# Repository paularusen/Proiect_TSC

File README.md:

## Descrierea produsului

  Proiectul este centrat pe microcontrolerul ```ESP32-C6```, care, datorită versatilității sale, suportă comunicații Wi‑Fi 6, 
Bluetooth și IEEE 802.15.4, alături de multiple interfețe periferice. Designul integrează un e‑paper display, un modul SD 
card, memorie flash externă, un modul RTC și interfețe de comunicație (```USB```, ```UART```, ```I2C```). Fiecare interfață este atribuită 
unor pini specifici pentru a asigura o separare clară a funcțiilor, evitând conflictele și maximizând performanța și
eficiența energetică.

## Diagrama bloc

## Descrierea componentelor și a pinilor utilizați

### ESP32-C6 – Microcontrolerul Central
Rol: Coordonează toate operațiunile sistemului și gestionează comunicațiile cu toate modulele periferice.
Pini atribuiți:

	- GND: 1 si 28
	- 3V3: 2
	- RESET: 3
	- SS_SD: 4
	- EPD_DC: 5
	- SCK: 6
	- MOSI: 7
	- INT_RTC: 8
	- 32KHZ: 9
	- GPIO8: 10
	- EPD_CS: 11
	- FLASH_CS: 12
	- USB_D-: 13
	- USB_D+: 14
	- IO/BOOT: 15
	- RTC_RST: 16
	- I2C_PW: 17
	- EPD_3V3_C: 18
	- SDA: 19
	- SCL: 20
	- EPD_RST: 21
	- IO/CHANGE: 23
	- RX: 24
	- TX: 25
	- EPD_BUSY: 26
	- MISO: 27

Rolul fiecărui pin va fi detaliat în cadrul componentelor, în următoarele rânduri.

### E‑Paper Display
Rol: Afișare informații într-un mod foarte eficient energetic, potrivit pentru aplicații de tip IoT sau afișaje statice.
Pini atribuiți:

	- EPD_DC: Selectează între modurile de comandă și de date pentru e-paper.
	- EPD_CS: Chip Select – activează comunicația cu e‑paper-ul.
	- EPD_RST: Linie de reset, esențială la inițializare pentru afișaj.
	- EPD_BUSY: Semnal de status ce indică dacă afișajul este ocupat (prevenind suprascrierea datelor).
	- EPD_3V3_C: Linia de alimentare dedicată, asigurând o tensiune stabilă și izolată pentru e‑paper.

### Modul SD Card
Rol: Stocare de date suplimentare (fișiere de sistem, date utilizator etc.)
Pini atribuiți:

	- SS_SD: Chip select specific pentru SD Card, activând modulul numai atunci când este necesar.
	- SCK: Linia de ceas pentru comunicațiile SPI.
	- MOSI: Linia de ieșire de date dinspre ESP32 către SD Card.
	- MISO: Linia de intrare de date, pentru citirea informațiilor de la SD Card.

### Memorie Flash Externă
Rol: Stocarea firmware-ului sau a datelor critice ce necesită o capacitate suplimentară față de memoria internă.
Pini atribuiți:

	- FLASH_CS: Chip select pentru memorie flash, pentru a activa comunicația doar atunci când este necesar.

### Modul RTC (Real-Time Clock)
Rol: Asigură o cronometrare precisă, utilă pentru funcții de alarmă, logare a datelor sau sincronizare de timp în 
aplicații IoT.
Pini atribuiți:

	- INT_RTC: Întrerupere de la RTC, notificând microcontrolerul despre evenimente (ex. alarmă).
	- RTC_RST: Linia de reset pentru modulul RTC, asigurând reinițializarea corectă a ceasului.
	- 32KHZ: Furnizează un semnal de 32 kHz, esențial pentru funcționarea precisă a RTC-ului.

### Senzorul de mediu (ex.: BME688):
Rol: Măsoară parametri esențiali precum temperatura, umiditatea, presiunea atmosferică și compoziția gazelor din mediul 
înconjurător.
Comunicarea se realizează prin magistrala I2C, utilizând SDA(linia de date I2C), SCL(linia de ceas I2C) și I2C_PW.

### Interfața I2C
Rol: Comunicare cu senzori, module de monitorizare a bateriei, eventual RTC suplimentar sau alte periferice cu consum 
redus.
Pini atribuiți:

	- SDA: Linia de date pentru comunicația I2C.
	- SCL: Linia de ceas pentru I2C.
	- I2C_PW: Poate fi folosit pentru a activa sau alimenta circuitele periferice I2C (ex. senzori sau monitor de baterie).

### Interfața USB
Rol: Programare, transfer de date sau alimentare în anumite condiții.
Pini atribuiți:

	- USB_D- și USB_D+: Linii diferențiale pentru comunicația USB.

### Interfața UART
Rol: Comunicații seriale pentru debugging, logare sau control extern.
Pini atribuiți:

	- RX: Recepție UART.
	- TX: Transmisie UART.

Pinii speciali precum IO/BOOT și IO/CHAGE permit configurarea modului de pornire și monitorizarea încărcării, iar GP0IO8 
și GOL asigură flexibilitatea pentru extinderi viitoare.
	IO/BOOT: utilizat la pornirea sistemului pentru selectarea modului de boot. Această funcție este esențială pentru a 
intra în modul de programare sau diagnosticare, conform cerințelor de firmware.
	IO/CHAGE: dedicat monitorizării stării de încărcare a sistemului. Acest pin poate fi legat la un circuit de detecție al 
încărcării bateriei sau indicator LED pentru a semnala starea de încărcare.
	GP0IO8: un GPIO general care poate fi folosit pentru extinderi ulterioare (ex. conectarea unui senzor adițional, trigger 
de eveniment etc.).
	Pin 22: funcționalitatea acestui pin poate fi folosită ca ieșire generală pentru semnale de control, cum ar fi activarea 
unor relee, indicatori LED suplimentari sau semnale de sincronizare pentru alte module.

## Consumul de Energie și comunicațiile

### Consumul microcontrolerului:
	- ESP32-C6 dispune de moduri de economisire a energiei (deep sleep) și este optimizat pentru aplicații IoT. Astfel, în 
condiții de standby consumul poate fi redus la câțiva microamperi.

### SPI și I2C:
	- Utilizarea magistralelor SPI (pentru SD Card, flash extern și e‑paper display) și I2C (pentru senzori și monitorizare 
baterie) permite un transfer de date rapid și eficient, dar și o separare logică care contribuie la reducerea 
interferențelor.

### USB și UART:
	- Aceste interfețe sunt folosite mai ales pentru debugging și programare. Deși USB poate implica un consum mai mare când 
este activ, acesta este activ doar în timpul programării sau transferurilor de date.

### Alimentare:
	- Pinul de 3V3) este utilizat pentru alimentarea ESP32-C6 și a modulelor critice, iar alocarea separată pentru EPD 
(EPD_3V3_C) asigură o tensiune stabilă pentru afișajul e-paper.

## Bill of Materials
| Componentă | Distribuitor | Datasheet |
| :---      | :---     | :---      |
| ESP32 C6| https://eu.mouser.com/ProductDetail/Espressif-Systems/ESP32-C6-WROOM-1U-N8?qs=1Kr7Jg1SGW%2FzPU4G%252ByMwkA%3D%3D | https://eu.mouser.com/datasheet/2/891/Espressif_Systems_7_11_2023_esp32_c6_wroom_1_wroom-3236277.pdf |
| BUTTON | https://www.digikey.ro/en/products/detail/bourns-inc/7914S-1-000E/2537971?s=N4IgTCBcDaIOwE4CMAWAygWiRgDHgoiALoC%2BQA | https://www.bourns.com/docs/Product-Datasheets/7914.pdf |
| USB-C connector| https://eu.mouser.com/ProductDetail/Same-Sky/UJC-H-G-SMT-2-P6-TR?qs=IKkN%2F947nfApFV8T6rOqww%3D%3D |https://eu.mouser.com/datasheet/2/1628/ujc_h_g_smt_2_p6_tr-3511211.pdf |
| USBLC6-2SC6Y | https://eu.mouser.com/ProductDetail/STMicroelectronics/USBLC6-2SC6Y?qs=gNDSiZmRJS%2FOgDexvXkdow%3D%3D | https://eu.mouser.com/datasheet/2/389/usblc6_2sc6y-1852505.pdf |
| DMG2305UX-7 | https://eu.mouser.com/ProductDetail/Diodes-Incorporated/DMG2305UX-7?qs=L1DZKBg7t5F%2FNBHrjfxC%252Bg%3D%3D | https://www.diodes.com/assets/Datasheets/DMG2305UX.pdf |
| XC6220A331MR-G | https://eu.mouser.com/ProductDetail/Torex-Semiconductor/XC6220A331MR-G?qs=AsjdqWjXhJ8ZSWznL1J0gg%3D%3D | https://eu.mouser.com/datasheet/2/760/xc6220-3371556.pdf |
| SD0805S020S1R0 | https://eu.mouser.com/ProductDetail/KYOCERA-AVX/SD0805S020S1R0?qs=jCA%252BPfw4LHbpkAoSnwrdjw%3D%3D | https://eu.mouser.com/datasheet/2/40/schottky-3165252.pdf |
| 112A-TAAR-R03 | https://store.comet.srl.ro/Catalogue/Product/43497/ | https://store.comet.bg/download-file.php?id=27596 |
| 68uH inductance | https://eu.mouser.com/ProductDetail/Vishay-Dale/IFDC5050JZER680M?qs=iLKYxzqNS745SePZd8tBoA%3D%3D | https://www.vishay.com/docs/34635/ifdc5050jz.pdf |
| SI1308EDL-T1-GE3 | https://eu.mouser.com/ProductDetail/Vishay-Semiconductors/SI1308EDL-T1-GE3?qs=bX1%252BNvsK%2FBramh9tgpOaEw%3D%3D | https://www.vishay.com/docs/63399/si1308edl.pdf |
| MBR0530 | https://eu.mouser.com/ProductDetail/Micro-Commercial-Components-MCC/MBR0530-TP?qs=KFo7JewZbUECRHkxGanrdg%3D%3D | https://eu.mouser.com/datasheet/2/258/MBR0520_MBR0580_SOD123_-2492194.pdf |
| MCP73831 | https://eu.mouser.com/ProductDetail/Microchip-Technology/MCP73831-2ACI-MC?qs=hH%252BOa0VZEiBneYTVdpuVdg%3D%3D | https://eu.mouser.com/datasheet/2/268/MCP73831_Family_Data_Sheet_DS20001984H-3441711.pdf |
| BME688 | https://eu.mouser.com/ProductDetail/Bosch-Sensortec/BME688?qs=IS%252B4QmGtzzqQoVDscqwx3A%3D%3D | https://eu.mouser.com/datasheet/2/783/bst_bme688_fl000-2307034.pdf |
| FH34SRJ-24S-0.5SH(99) | https://eu.mouser.com/ProductDetail/Hirose-Connector/FH34SRJ-24S-0.5SH99?qs=vcbW%252B4%252BSTIpKBl5ap9J8Fw%3D%3D | https://eu.mouser.com/datasheet/2/185/FH34SRJ_24S_0_5SH_99__CL0580_1255_6_99_2DDrawing_0-1615044.pdf |
| BD5229G-TR | https://eu.mouser.com/ProductDetail/ROHM-Semiconductor/BD5229G-TR?qs=4kLU8WoGk0vvnhrrYwdszw%3D%3D | https://fscdn.rohm.com/en/products/databook/datasheet/ic/power/voltage_detector/bd52xxg-e.pdf |
| MAX17048G+T10 | https://eu.mouser.com/ProductDetail/Analog-Devices-Maxim-Integrated/MAX17048G%2bT10?qs=D7PJwyCwLAoGnnn8jEPRBQ%3D%3D | https://eu.mouser.com/datasheet/2/609/MAX17048_MAX17049-3469099.pdf |
| DS3231SN# | https://eu.mouser.com/ProductDetail/Analog-Devices-Maxim-Integrated/DS3231SN?qs=1eQvB6Dk1vhUlr8%2FOrV0Fw%3D%3D | https://eu.mouser.com/datasheet/2/609/DS3231-3421123.pdf |
| CPH3225A | https://eu.mouser.com/ProductDetail/Seiko-Semiconductors/CPH3225A?qs=3etwrb1wR%252BhUOph6lAO7eg%3D%3D | https://eu.mouser.com/datasheet/2/360/Seiko_Instruments_MicroBattery_E_20230330_2024Jan_-3561061.pdf |
| PFMF.050.1 | https://eu.mouser.com/ProductDetail/Schurter/PFMF.050.2?qs=1auRipcfynCums5v1iucSA%3D%3D | https://eu.mouser.com/datasheet/2/358/typ_PFMF-1275918.pdf |
| Qwiic | https://eu.mouser.com/ProductDetail/Adafruit/4208?qs=PzGy0jfpSMtbScLbr0L5dw%3D%3D | https://learn.adafruit.com/introducing-adafruit-stemma-qt/technical-specs |
| W25Q512JVEIQ | https://eu.mouser.com/ProductDetail/Winbond/W25Q512JVEIQ?qs=l7cgNqFNU1jw6svr3at6tA%3D%3D | https://eu.mouser.com/datasheet/2/949/Winbond_W25Q512JV_Datasheet-3240039.pdf |
| PGB1010603MR | https://eu.mouser.com/ProductDetail/Littelfuse/PGB1010603MR?qs=gu7KAQ731URLg4GSnNNN7Q%3D%3D | https://www.littelfuse.com/assetdocs/pulseguard-esd-suppressors-pgb1-datasheet?assetguid=8a337998-d54d-466b-be4e-dc5bcd1f9321 |
| TANT Capacitor | https://eu.mouser.com/ProductDetail/KEMET/T491B107M006AT?qs=U312oeP%2FpiHOgyk6KO2m0g%3D%3D | https://www.vishay.com/docs/40002/293d.pdf |
| Capacitor 0.1uF | https://eu.mouser.com/ProductDetail/KYOCERA-AVX/KGF21BR71H104KT?qs=Jm2GQyTW%2FbjYyKCvVWAEOw%3D%3D | https://eu.mouser.com/datasheet/2/40/KGF-3223650.pdf |
| Capacitor 1uF | https://eu.mouser.com/ProductDetail/TAIYO-YUDEN/MAASL105CC7105MFCA01?qs=HFfMDpzxxd1Fn%2FInbJA7vw%3D%3D | https://eu.mouser.com/datasheet/2/396/TAIYO_YUDEN_04_27_2024_c_mlcc_A_e1-3451516.pdf |
| Capacitor 4.7uF | https://eu.mouser.com/ProductDetail/KYOCERA-AVX/CM05X5R475M16AH?qs=doiCPypUmgFT1xquZKhWtQ%3D%3D | https://eu.mouser.com/datasheet/2/40/Kyocera_AVX_Components_CM025_CM05_CM105_CM21_E217K-2932876.pdf |
| Capacitor 10 uF | https://eu.mouser.com/ProductDetail/TDK/CGA3EDX7T1A106M080AU?qs=ZcfC38r4PovL%2FBNBUzzBFw%3D%3D | https://product.tdk.com/system/files/dam/doc/product/capacitor/ceramic/mlcc/catalog/mlcc_automotive_general_en.pdf |
| Capacitor 100nF | https://eu.mouser.com/ProductDetail/KYOCERA-AVX/KAM21BR71H104JT?qs=Jm2GQyTW%2Fbic6Zk4McEt6w%3D%3D | https://eu.mouser.com/datasheet/2/40/AutoMLCCKAM-3216307.pdf |
| Resistor 0.47 | https://eu.mouser.com/ProductDetail/SEI-Stackpole/RNCL1210FT50L0?qs=17ckDYBRdelVLOJ%252BDFjlUw%3D%3D | https://eu.mouser.com/datasheet/2/385/sei_rncl-3223524.pdf |
| Resistor 2.2 | https://eu.mouser.com/ProductDetail/YAGEO/RT1206FRE072R2L?qs=XhSZopxZ3H6S0nYZD83pAA%3D%3D | https://eu.mouser.com/datasheet/2/447/PYu_RT_1_to_0_01_RoHS_L_15-3461507.pdf |
| Resistor 15 | https://eu.mouser.com/ProductDetail/Panasonic/ERA-6AHD150V?qs=MNPzkKEzRtQip8ZeekU%252BRw%3D%3D | https://industrial.panasonic.com/cdbs/www-data/pdf/RDM0000/AOA0000C307.pdf |
Resistor 200 | https://eu.mouser.com/ProductDetail/TE-Connectivity-Holsworthy/RP73C2B200RFTDF?qs=n4i9pByFsMR0dWGpf721CA%3D%3D | https://eu.mouser.com/datasheet/2/418/10/ENG_DS_1773272_M1-1588495.pdf |
| Resistor 2k | https://eu.mouser.com/ProductDetail/Panasonic/ERA-3AED202V?qs=yocZuyCaXdM2cBmjcGkIyA%3D%3D | https://industrial.panasonic.com/cdbs/www-data/pdf/RDM0000/AOA0000C307.pdf |
| Resistor 5k1 | https://eu.mouser.com/ProductDetail/Vishay-Beyschlag/MCS04020C5101FE000?qs=wTZ%2FFzl837YsKPLPRIXUbg%3D%3D | https://www.vishay.com/docs/28705/mcx0x0xpro.pdf |
| Resistor 10k | https://eu.mouser.com/ProductDetail/SEI-Stackpole/RNWA0612BTE10K0?qs=IKkN%2F947nfD62pDKWE9ZTQ%3D%3D | https://eu.mouser.com/datasheet/2/385/SEI_RNWA-3473840.pdf |
| Resistor 100K | https://eu.mouser.com/ProductDetail/Panasonic/ERA-3AED104V?qs=MNPzkKEzRtQIWcmUWL4kjg%3D%3D | https://industrial.panasonic.com/cdbs/www-data/pdf/RDM0000/AOA0000C307.pdf |
| E-Paper Display | https://eu.mouser.com/ProductDetail/Microtips-Technology/MT-DEPG0750BNU590F1?qs=DPoM0jnrROVRMMTX0WzK%252Bw%3D%3D| https://eu.mouser.com/datasheet/2/271/MT_DEPG0750BNU590F1_V2_7-1894282.pdf |
| LP584174 Battery| https://www.tme.eu/en/details/accu-lp584174_cl/rechargeable-batteries/cellevia-batteries/l584174/ | https://www.tme.eu/Document/e0683d8c34e6d878124489f71bffb6ee/cel0014.pdf |

## Observații
- Am modificat footprint-ul componentei J2, prin mutarea pad-urilor GND, VUSB și B8 cu câțiva mm spre stânga, pentru a corecta eroarea ”SMD Hole”.

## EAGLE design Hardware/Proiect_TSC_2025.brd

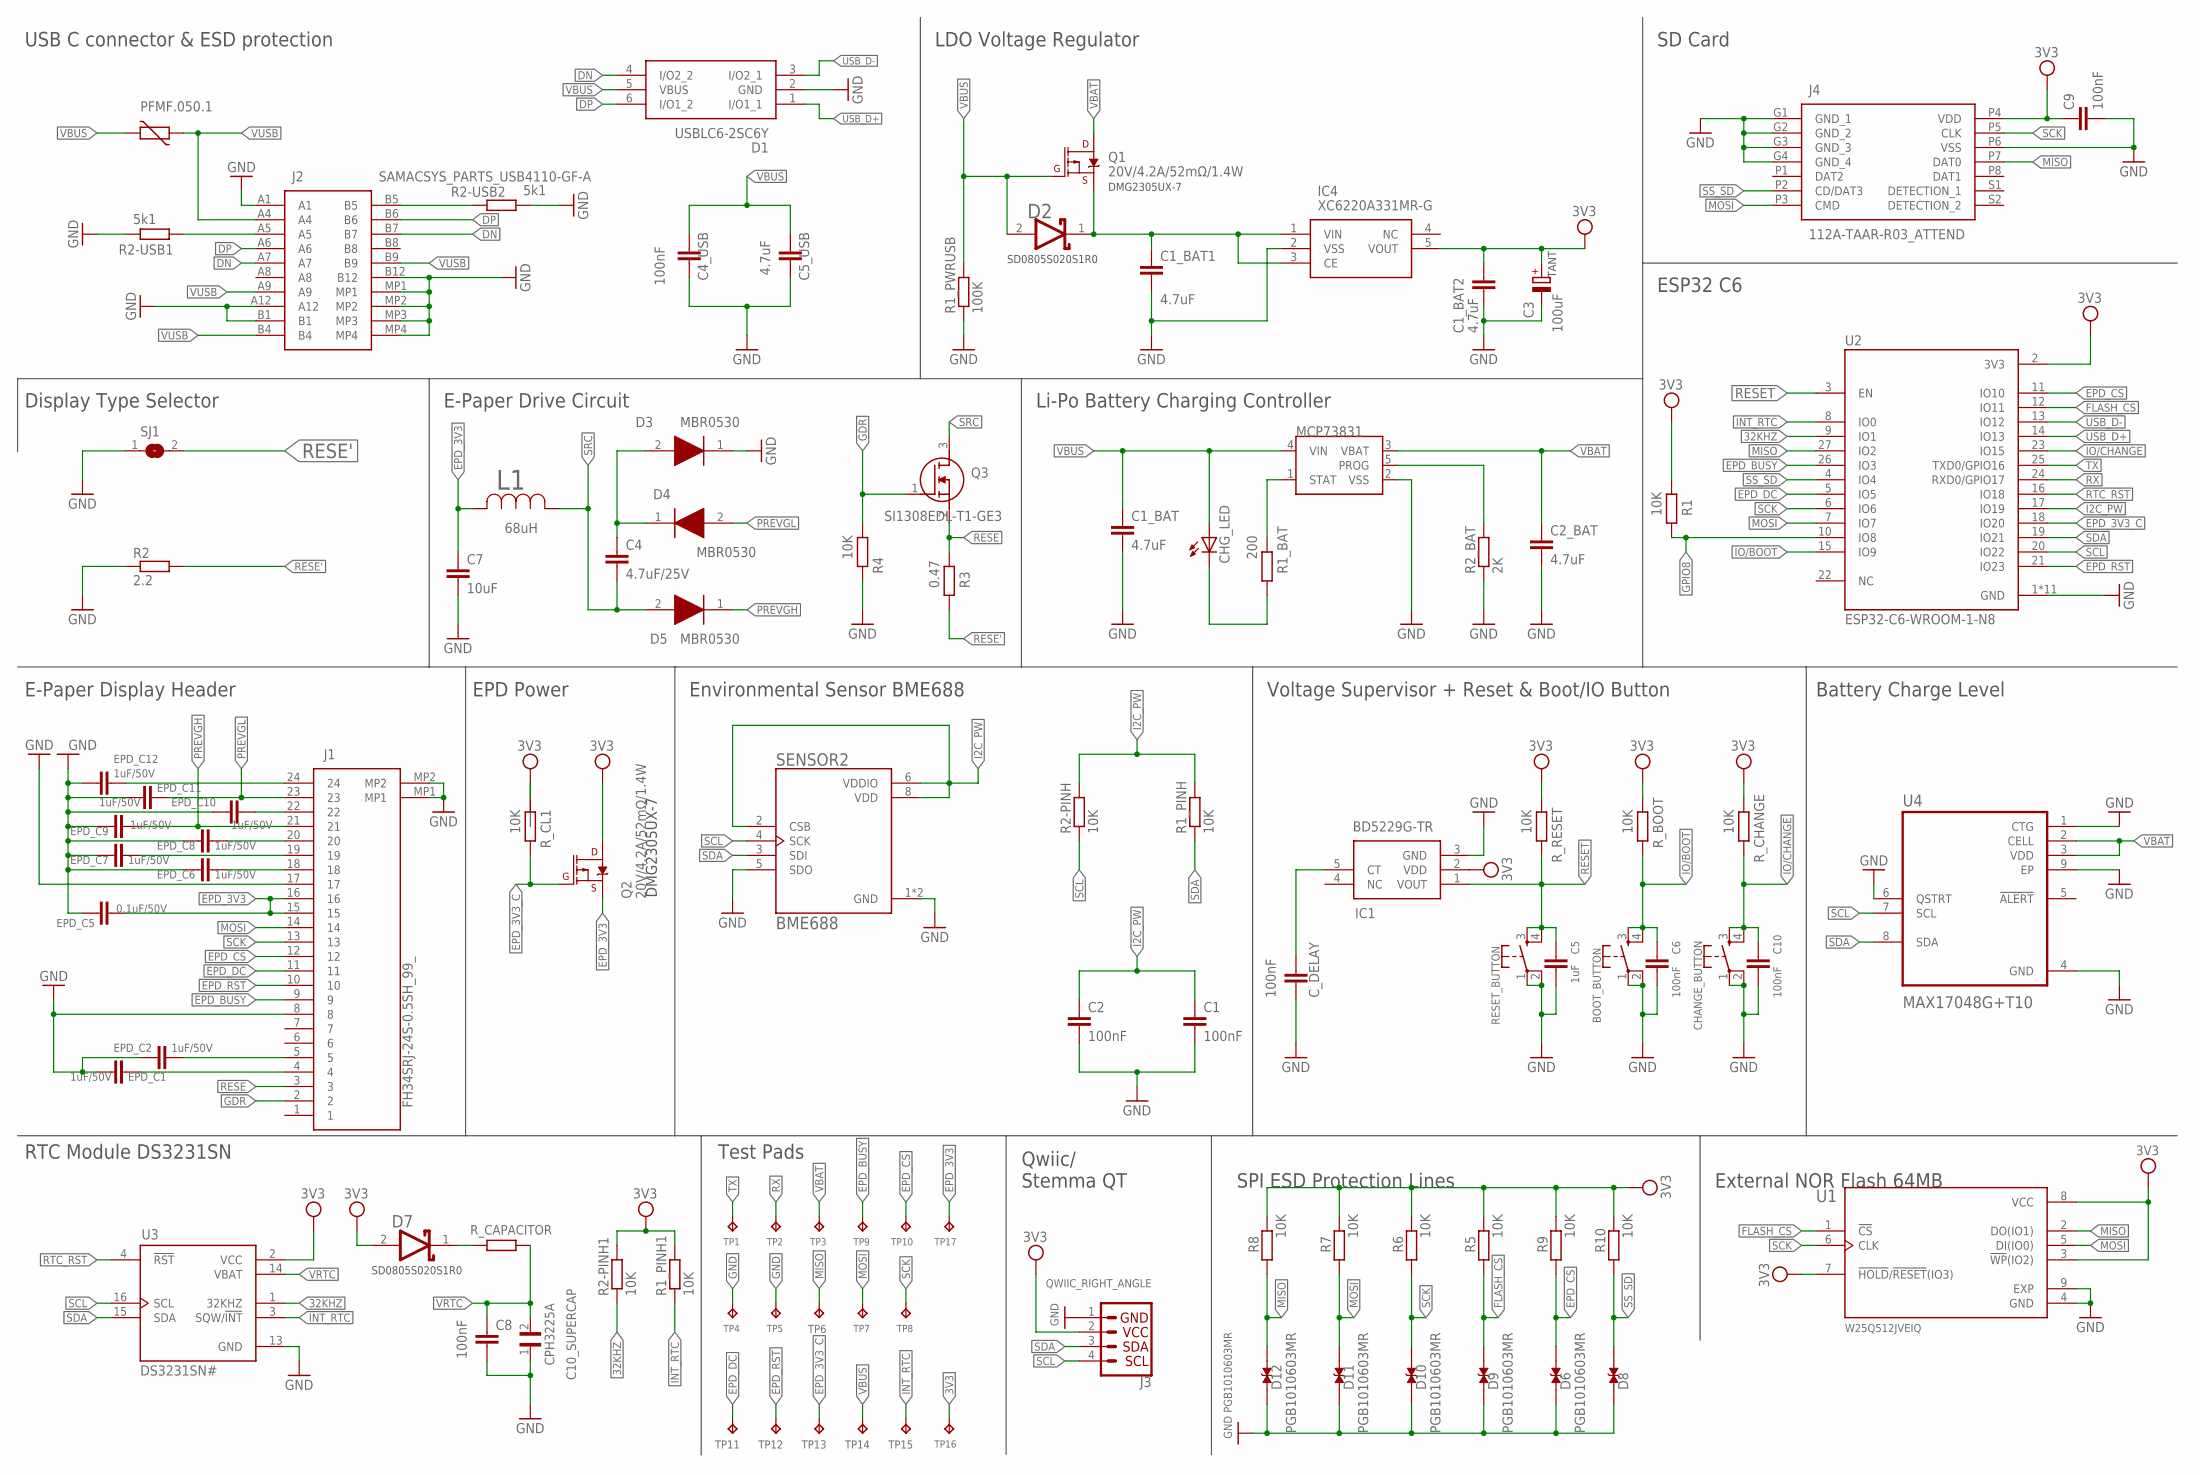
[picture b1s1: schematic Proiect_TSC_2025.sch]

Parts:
BOOT_BUTTON: BUTTON_CUSYOMV1; MYBUTTON
C1, C2, C6, C8, C9, C10: 100nF; ESP32_WROVER_EAGLE-LTSPICE_C0402
C1_BAT, C1_BAT1, C1_BAT2, C2_BAT: 4.7uF; ESP32_WROVER_EAGLE-LTSPICE_C0402
C3: 100uF; RCL_CT3528
C4: 4.7uF/25V; ESP32_WROVER_EAGLE-LTSPICE_C0402
C4_USB: 100nF; EAGLE-LTSPICE_C0402
C5: 1uF; ESP32_WROVER_EAGLE-LTSPICE_C0402
C5_USB: 4.7uF; EAGLE-LTSPICE_C0402
C7: 10uF; ESP32_WROVER_EAGLE-LTSPICE_C0402
C10_SUPERCAP: CPH3225A; CAPCP3225X100N
CHANGE_BUTTON: CHANGE_BUTTON; MYBUTTON
CHG_LED: ADAFRUIT_LEDCHIP-LED0603; ADAFRUIT_CHIP-LED0603
C_DELAY: 100nF; ESP32_WROVER_EAGLE-LTSPICE_C0402
D1: USBLC6-2SC6Y; SOT95P280X145-6N
D2: ESP32_WROVER_AVX---SD0805S020S1R0_AVX_SD0805S020S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; ESP32_WROVER_AVX---SD0805S020S1R0_AVX_SD0805S020S1R0_0
D3, D4, D5: MBR0530; SOD3716X135N
D6, D8, D9, D10, D11, D12: PGB1010603MR; DIOC1608X36N
D7: SD0805S020S1R0; ESP32_WROVER_AVX---SD0805S020S1R0_AVX_SD0805S020S1R0_0
EPD_C1, EPD_C2, EPD_C6, EPD_C7, EPD_C8, EPD_C9, EPD_C10, EPD_C11, EPD_C12: 1uF/50V; ESP32_WROVER_EAGLE-LTSPICE_C0402
EPD_C5: 0.1uF/50V; ESP32_WROVER_EAGLE-LTSPICE_C0402
IC1: BD5229G-TR; SOT95P280X125-5N
IC4: XC6220A331MR-G; SOT95P280X120-5N
J1: FH34SRJ-24S-0.5SH_99_; FH34SRJ24S05SH99
J2: SAMACSYS_PARTS_USB4110-GF-A; SAMACSYS_PARTS_USB4110GFA
J3: QWIIC_RIGHT_ANGLE; JST04_1MM_RA
J4: 112A-TAAR-R03_ATTEND; 112ATAARR03ATTEND
L1: 68uH; IND_4828-WE-TPC_WRE
MCP73831: MCP73831; ESP32_WROVER_SPARKFUN-IC-POWER_SOT23-5
PFMF.050.1: ESP32C6_VARISTORCN1812; ESP32C6_VARISTOR_CT/CN1812
Q1, Q2: 20V/4.2A/52mΩ/1.4W; ESP32_WROVER_SPARKFUN-DISCRETESEMI_SOT23-3
Q3: SI1308EDL-T1-GE3; SOT65P210X110-3N
R1, R1_PINH, R1_PINH1, R2-PINH, R2-PINH1, R4, R5, R6, R7, R8, R9, R10: 10K; ESP32_WROVER_EAGLE-LTSPICE_R0402
R1_BAT: 200; ESP32_WROVER_EAGLE-LTSPICE_R0402
R1_PWRUSB: 100K; ESP32_WROVER_EAGLE-LTSPICE_R0402
R2: 2.2; ESP32_WROVER_EAGLE-LTSPICE_R0402
R2-USB1, R2-USB2: 5k1; ESP32_WROVER_EAGLE-LTSPICE_R0402
R2_BAT: 2K; ESP32_WROVER_EAGLE-LTSPICE_R0402
R3: 0.47; ESP32_WROVER_EAGLE-LTSPICE_R0402
RESET_BUTTON: BUTTON_CUSYOMV1; MYBUTTON
R_BOOT: 10K; ESP32_WROVER_EAGLE-LTSPICE_R0402
R_CAPACITOR: ESP32_WROVER_EAGLE-LTSPICE_RR0402; ESP32_WROVER_EAGLE-LTSPICE_R0402
R_CHANGE: 10K; ESP32_WROVER_EAGLE-LTSPICE_R0402
R_CL1: 10K; ESP32_WROVER_EAGLE-LTSPICE_R0402
R_RESET: 10K; ESP32_WROVER_EAGLE-LTSPICE_R0402
SENSOR2: BME688; ESP32_WROVER_BME680_PSON80P300X300X100-8N
SJ1: 0; SJ
TP1, TP2, TP3, TP4, TP5, TP6, TP7, TP8, TP9, TP10, TP11, TP12, TP13, TP14, TP15, TP16, TP17: TPTP20R; TP20R
U1: W25Q512JVEIQ; SON127P600X800X80-9N
U2: ESP32-C6-WROOM-1-N8; XCVR_ESP32-C6-WROOM-1-N8
U3: DS3231SN#; SOIC127P1032X265-16N
U4: MAX17048G+T10; SON50P200X200X80-9N

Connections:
3V3: C1_BAT2.1, C3.+, C9.1, D7.2 (ANODE), IC1.2 (VDD), IC4.5 (VOUT), J3.2, J4.P4 (VDD), Q2.3 (D), R1.2, R1_PINH1.2, R2-PINH1.2, R5.2, R6.2, R7.2, R8.2, R9.2, R10.2, R_BOOT.2, R_CHANGE.2, R_CL1.2, R_RESET.2, TP16.TP, U1.3 (!WP!(IO2)), U1.7 (!HOLD!/!RESET!(IO3)), U1.8 (VCC), U2.2 (3V3), U3.2 (VCC)
32KHZ: R2-PINH1.1, U2.9 (IO1), U3.1 (32KHZ)
DN: D1.4 (I/O2_2), J2.A7, J2.B7
DP: D1.6 (I/O1_2), J2.A6, J2.B6
EPD_3V3: C7.1, EPD_C5.2, J1.15, J1.16, L1.2, Q2.2 (S), TP17.TP
EPD_3V3_C: Q2.1 (G), R_CL1.1, TP13.TP, U2.18 (IO20)
EPD_BUSY: J1.9, TP9.TP, U2.26 (IO3)
EPD_CS: D6.2, J1.12, R9.1, TP10.TP, U2.11 (IO10)
EPD_DC: J1.11, TP11.TP, U2.5 (IO5)
EPD_RST: J1.10, TP12.TP, U2.21 (IO23)
FLASH_CS: D9.2, R5.1, U1.1 (!CS), U2.12 (IO11)
GDR: J1.2, Q3.1 (G), R4.2
GND: BOOT_BUTTON.1, BOOT_BUTTON.2, C1.2, C1_BAT.2, C1_BAT1.2, C1_BAT2.2, C2.2, C2_BAT.2, C3.-, C4_USB.2, C5.2, C5_USB.2, C6.2, C7.2, C8.2, C9.2, C10.2, C10_SUPERCAP.1, CHANGE_BUTTON.1, CHANGE_BUTTON.2, C_DELAY.2, D1.2 (GND), D3.1 (K), D6.1, D8.1, D9.1, D10.1, D11.1, D12.1, EPD_C1.2, EPD_C2.2, EPD_C5.1, EPD_C6.2, EPD_C7.2, EPD_C8.2, EPD_C9.2, EPD_C10.2, EPD_C11.2, EPD_C12.2, IC1.3 (GND), IC4.2 (VSS), J1.8, J1.17, J1.MP1, J1.MP2, J2.A1, J2.A12, J2.B1, J2.B12, J2.MP1, J2.MP2, J2.MP3, J2.MP4, J3.1, J4.G1 (GND_1), J4.G2 (GND_2), J4.G3 (GND_3), J4.G4 (GND_4), J4.P6 (VSS), MCP73831.2 (VSS), R1_PWRUSB.1, R2.1, R2-USB1.1, R2-USB2.2, R2_BAT.1, R4.1, RESET_BUTTON.1, RESET_BUTTON.2, SENSOR2.1 (GND), SENSOR2.5 (SDO), SENSOR2.7 (GND), SJ1.1, TP4.TP, TP5.TP, U1.4 (GND), U1.9 (EXP), U2.1 (GND), U2.28 (GND), U2.29_1 (GND), U2.29_2 (GND), U2.29_3 (GND), U2.29_4 (GND), U2.29_5 (GND), U2.29_6 (GND), U2.29_7 (GND), U2.29_8 (GND), U2.29_9 (GND), U3.13 (GND), U4.1 (CTG), U4.4 (GND), U4.6 (QSTRT), U4.9 (EP)
GPIO8: R1.1, U2.10 (IO8)
I2C_PW: C1.1, C2.1, R1_PINH.2, R2-PINH.2, SENSOR2.2 (CSB), SENSOR2.6 (VDDIO), SENSOR2.8 (VDD), U2.17 (IO19)
INT_RTC: R1_PINH1.1, TP15.TP, U2.8 (IO0), U3.3 (SQW/!INT)
IO/BOOT: BOOT_BUTTON.3, BOOT_BUTTON.4, C6.1, R_BOOT.1, U2.15 (IO9)
IO/CHANGE: C10.1, CHANGE_BUTTON.3, CHANGE_BUTTON.4, R_CHANGE.1, U2.23 (IO15)
MISO: D12.2, J4.P7 (DAT0), R8.1, TP6.TP, U1.2 (DO(IO1)), U2.27 (IO2)
MOSI: D11.2, J1.14, J4.P3 (CMD), R7.1, TP7.TP, U1.5 (DI(IO0)), U2.7 (IO7)
unnamed: J2.A5, R2-USB1.2
unnamed: J2.B5, R2-USB2.1
unnamed: C1_BAT1.1, D2.1 (CATHODE), IC4.1 (VIN), IC4.3 (CE), Q1.2 (S)
unnamed: C4.1, D3.2 (A), D4.1 (K)
unnamed: CHG_LED.C, R1_BAT.1
unnamed: MCP73831.1 (STAT), R1_BAT.2
unnamed: MCP73831.5 (PROG), R2_BAT.2
unnamed: EPD_C1.1, J1.4
unnamed: EPD_C2.1, J1.5
unnamed: EPD_C6.1, J1.18
unnamed: EPD_C7.1, J1.19
unnamed: EPD_C8.1, J1.20
unnamed: EPD_C10.1, J1.22
unnamed: EPD_C12.1, J1.24
unnamed: C_DELAY.1, IC1.5 (CT)
unnamed: D7.1 (CATHODE), R_CAPACITOR.2
PREVGH: D5.1 (K), EPD_C9.1, J1.21
PREVGL: D4.2 (A), EPD_C11.1, J1.23
RESE: J1.3, Q3.2 (S), R3.2
RESE': R2.2, R3.1, SJ1.2
RESET: C5.1, IC1.1 (VOUT), RESET_BUTTON.3, RESET_BUTTON.4, R_RESET.1, U2.3 (EN)
RTC_RST: U2.16 (IO18), U3.4 (!RST)
RX: TP2.TP, U2.24 (RXD0/GPIO17)
SCK: D10.2, J1.13, J4.P5 (CLK), R6.1, TP8.TP, U1.6 (CLK), U2.6 (IO6)
SCL: J3.4, R2-PINH.1, SENSOR2.4 (SCK), U2.20 (IO22), U3.16 (SCL), U4.7 (SCL)
SDA: J3.3, R1_PINH.1, SENSOR2.3 (SDI), U2.19 (IO21), U3.15 (SDA), U4.8 (SDA)
SRC: C4.2, D5.2 (A), L1.1, Q3.3 (D)
SS_SD: D8.2, J4.P2 (CD/DAT3), R10.1, U2.4 (IO4)
TX: TP1.TP, U2.25 (TXD0/GPIO16)
USB_D+: D1.1 (I/O1_1), U2.14 (IO13)
USB_D-: D1.3 (I/O2_1), U2.13 (IO12)
VBAT: C2_BAT.1, MCP73831.3 (VBAT), Q1.3 (D), TP3.TP, U4.2 (CELL), U4.3 (VDD)
VBUS: C1_BAT.1, C4_USB.1, C5_USB.1, CHG_LED.A, D1.5 (VBUS), D2.2 (ANODE), MCP73831.4 (VIN), PFMF.050.1.2, Q1.1 (G), R1_PWRUSB.2, TP14.TP
VRTC: C8.1, C10_SUPERCAP.2, R_CAPACITOR.1, U3.14 (VBAT)
VUSB: J2.A4, J2.A9, J2.B4, J2.B9, PFMF.050.1.1

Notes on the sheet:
USB C connector & ESD protection
LDO Voltage Regulator
SD Card
DMG2305UX-7
SD0805S020S1R0
TANT
ESP32 C6
Display Type Selector
E-Paper Drive Circuit
Li-Po Battery Charging Controller
E-Paper Display Header
EPD Power
Environmental Sensor BME688
Battery Charge Level
Voltage Supervisor + Reset & Boot/IO Button
External NOR Flash 64MB
SPI ESD Protection Lines
RTC Module DS3231SN
Test Pads
Qwiic/ Stemma QT

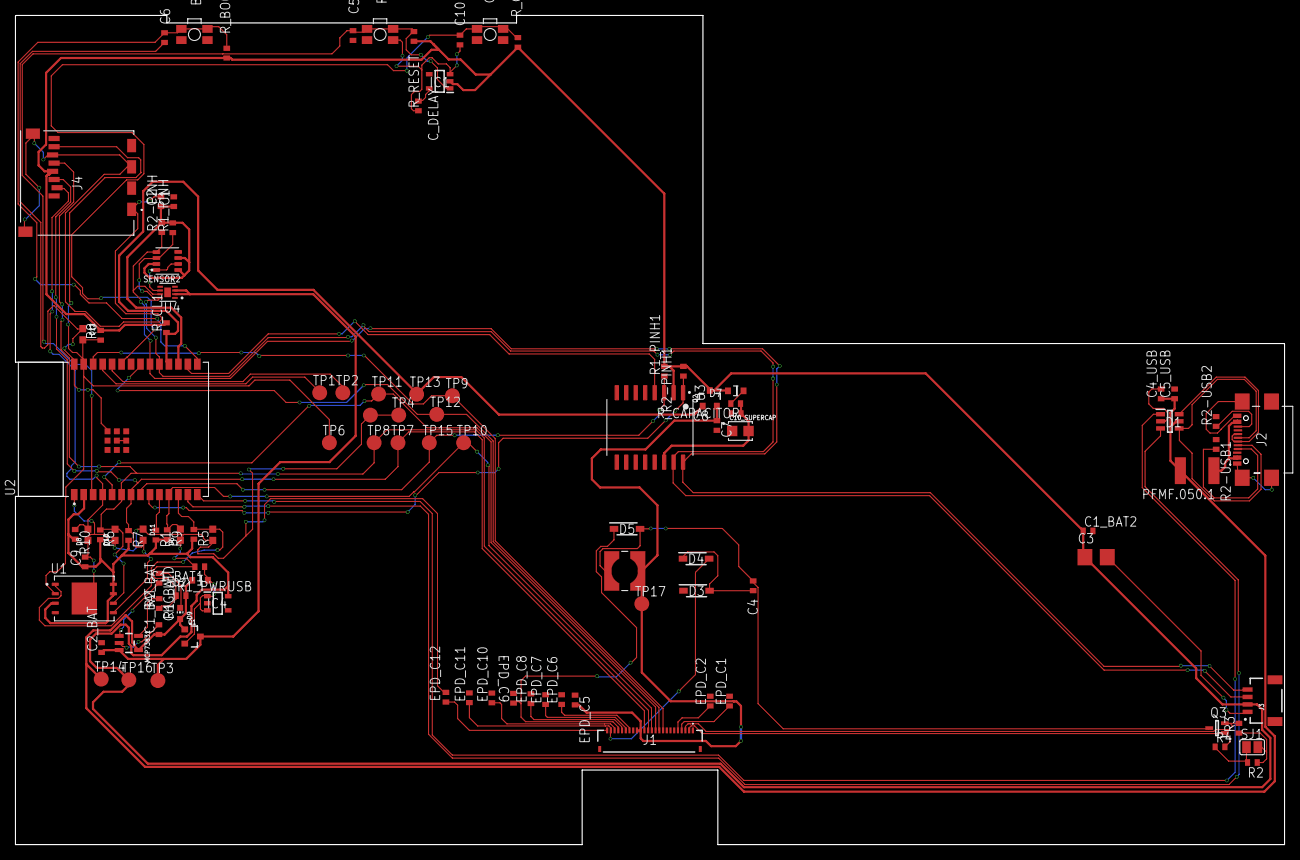
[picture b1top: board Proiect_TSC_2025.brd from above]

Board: 2 copper layers, 170.2 x 111.2 mm, 103 parts (0 on the bottom side), 55 nets.

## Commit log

2025-03-31 Create LICENSE
2025-04-06 Added 3D model of the device
2025-04-12 Delete Hardware/Proiect_TSC_2025.brd
    Deleted old version of this file.
2025-04-12 Delete Hardware/Proiect_TSC_2025.sch
    Deleted old version of this file.
2025-04-12 Add files via upload
    Added the new modified files according to the review.
2025-04-12 Rename Proiect_TSC_2025_NEW v41.csv to Bill of Materials.csv
2025-04-12 Delete Mechanical/Openbook reader.zip
    Deleted the old version of this file.
2025-04-12 Delete images/3D_board_front.png
    Deleted this picture because it doesnt correspond with the new version of the board.
2025-04-12 Rename images to Images
2025-04-12 Update README.md
    Added BOM table and block diagram
2025-04-12 Rename OpenBook reader Drawing.pdf to OpenBook_E-Reader_Drawing.pdf
2025-04-12 Rename Diagrama_bloc.png to Images/Diagrama_bloc.png

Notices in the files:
parts and their libraries:
COPYRIGHT: Copyright (C) 2024 Ultra Librarian. All rights reserved.
